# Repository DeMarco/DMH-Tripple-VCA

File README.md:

# DMH-Tripple-VCA
3x transistor based VCA on same panel

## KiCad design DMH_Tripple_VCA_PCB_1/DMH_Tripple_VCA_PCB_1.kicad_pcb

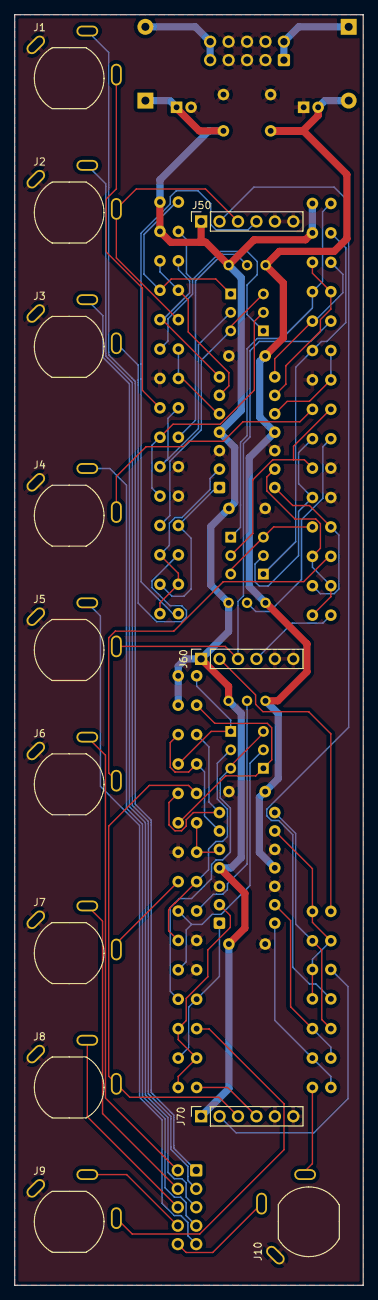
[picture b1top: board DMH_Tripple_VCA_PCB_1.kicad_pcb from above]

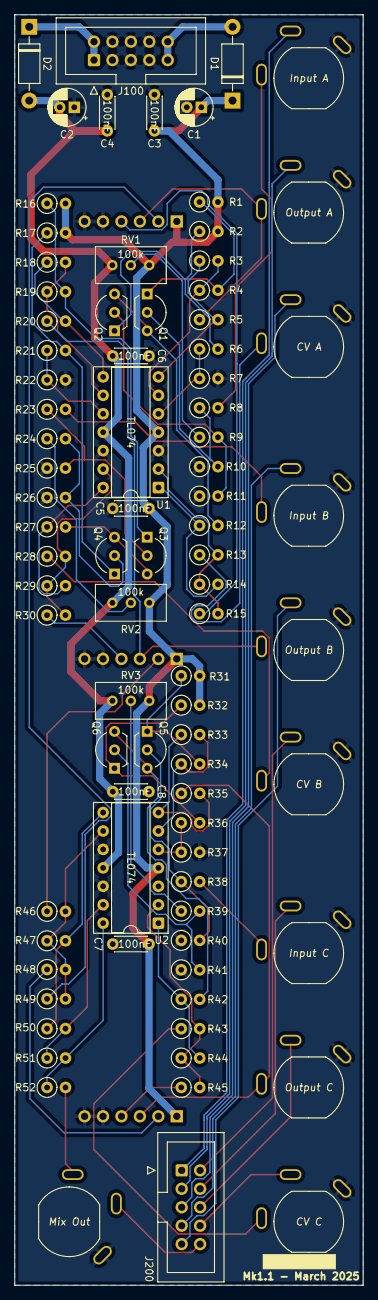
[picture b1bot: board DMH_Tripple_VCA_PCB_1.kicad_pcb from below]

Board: 2 copper layers, 48.0 x 175.0 mm, 88 parts (75 on the bottom side), 68 nets.

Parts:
C1, C2: 47uF; CP_Radial_D5.0mm_P2.00mm
C3, C4, C5, C6, C7, C8: 100nF; C_Disc_D4.3mm_W1.9mm_P5.00mm
D1: SB140+; D_DO-41_SOD81_P10.16mm_Horizontal
D2: SB140-; D_DO-41_SOD81_P10.16mm_Horizontal
J1, J2, J3, J4, J5, J6, J7, J8, J9, J10: TS_Jack_6.35mm_Sw; CUI_MJ-63052A
J50, J60, J70: Conn_01x06; PinSocket_1x06_P2.54mm_Vertical
J100: IDC_02x05; IDC-Header_2x05_P2.54mm_Vertical_Eurorack
J200: IDC_02x05; IDC-Header_2x05_P2.54mm_Vertical_BackBone
Q1, Q2, Q3, Q4, Q5, Q6: BC548; TO-92L_Inline_Wide
R1, R2, R16, R17, R31, R32: 20k; R_Axial_DIN0207_L6.3mm_D2.5mm_P2.54mm_Vertical
R3, R7, R8, R9, R13, R14, R15, R18, R22, R23, R24, R28, R29, R30, R33, R37, R38, R39, R43, R44, R45, R46, R47, R48, R49, R50, R51: 100k; R_Axial_DIN0207_L6.3mm_D2.5mm_P2.54mm_Vertical
R4, R6, R12, R19, R21, R27, R34, R36, R42: 10k; R_Axial_DIN0207_L6.3mm_D2.5mm_P2.54mm_Vertical
R5, R20, R35, R52: 1k; R_Axial_DIN0207_L6.3mm_D2.5mm_P2.54mm_Vertical
R10, R11, R25, R26, R40, R41: 100R; R_Axial_DIN0207_L6.3mm_D2.5mm_P2.54mm_Vertical
RV1, RV2, RV3: 100k; Potentiometer_Bourns_3296W_Vertical
U1, U2: TL074; DIP-14_W7.62mm_Socket

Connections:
+12V: C1.1, C3.1, C5.1, C7.1, D1.1 (K), J50.1, J60.1, J70.1, R1.2, R2.2, R16.2, R17.2, R31.2, R32.2, RV1.3, RV2.3, RV3.3, U1.4 (V+), U2.4 (V+)
-12V: C2.2, C4.2, C6.2, C8.2, D2.2 (A), RV1.1, RV2.1, RV3.1, U1.11 (V-), U2.11 (V-)
/Inputs and Outputs/CV A Jack: J3.T, R13.1
/Inputs and Outputs/CV B Jack: J6.T, R28.1
/Inputs and Outputs/CV C Jack: J9.T, R43.1
/Inputs and Outputs/Input A Jack: J1.T, R8.2
/Inputs and Outputs/Input B Jack: J4.T, R23.2
/Inputs and Outputs/Input C Jack: J7.T, R38.2
/Inputs and Outputs/Mix Out Jack: J10.T, R52.2
/Inputs and Outputs/Mute A Switch: J50.2, R49.1
/Inputs and Outputs/Mute B Switch: J60.2, R46.1
/Inputs and Outputs/Mute C Switch: J70.2, R48.1
/Inputs and Outputs/Offset A Pot: J50.4, R15.1
/Inputs and Outputs/Offset B Pot: J60.4, R30.1
/Inputs and Outputs/Offset C Pot: J70.4, R45.1
/Inputs and Outputs/Output A Jack: J2.T, J50.3, R5.1
/Inputs and Outputs/Output B Jack: J5.T, J60.3, R20.1
/Inputs and Outputs/Output C Jack: J8.T, J70.3, R35.1
GND: C1.2, C2.1, C3.2, C4.1, C5.2, C6.1, C7.2, C8.1, J1.S, J2.S, J3.S, J4.S, J5.S, J6.S, J7.S, J8.S, J9.S, J10.S, J50.5, J50.6, J60.5, J60.6, J70.5, J70.6, J100.2a, J100.2b, J100.3a, J100.3b, J100.4a, J100.4b, R7.2, R10.1, R11.1, R22.2, R25.1, R26.1, R37.2, R40.1, R41.1, U1.3 (+), U1.12 (+), U2.3 (+), U2.10 (+), U2.12 (+)
unnamed: D1.2 (A), J100.5a, J100.5b
unnamed: D2.1 (K), J100.1a, J100.1b
unnamed: J1.TN, J200.1
unnamed: J2.TN, J200.2
unnamed: J3.TN, J200.3
unnamed: J4.TN, J200.4
unnamed: J5.TN, J200.5
unnamed: J6.TN, J200.6
unnamed: J7.TN, J200.7
unnamed: J8.TN, J200.8
unnamed: J9.TN, J200.9
unnamed: J10.TN, J200.10
unnamed: Q1.2 (B), R8.1, R10.2
unnamed: Q1.1 (C), R1.1, R4.2
unnamed: Q1.3 (E), Q2.3 (E), R12.2
unnamed: Q2.2 (B), R9.2, R11.2
unnamed: Q2.1 (C), R2.1, R6.2
unnamed: Q3.2 (B), R23.1, R25.2
unnamed: Q3.1 (C), R16.1, R19.2
unnamed: Q3.3 (E), Q4.3 (E), R27.2
unnamed: Q4.2 (B), R24.2, R26.2
unnamed: Q4.1 (C), R17.1, R21.2
unnamed: Q5.2 (B), R38.1, R40.2
unnamed: Q5.1 (C), R31.1, R34.2
unnamed: Q5.3 (E), Q6.3 (E), R42.2
unnamed: Q6.2 (B), R39.2, R41.2
unnamed: Q6.1 (C), R32.1, R36.2
unnamed: R3.1, R5.2, U1.7
unnamed: R9.1, RV1.2
unnamed: R12.1, R14.2, U1.1
unnamed: R18.1, R20.2, U1.8
unnamed: R24.1, RV2.2
unnamed: R27.1, R29.2, U1.14
unnamed: R33.1, R35.2, U2.7
unnamed: R39.1, RV3.2
unnamed: R42.1, R44.2, U2.1
unnamed: R47.2, R50.1, U2.8
unnamed: R51.2, R52.1, U2.14
unnamed: R13.2, R14.1, R15.2, U1.2 (-)
unnamed: R6.1, R7.1, U1.5 (+)
unnamed: R3.2, R4.1, U1.6 (-)
unnamed: R21.1, R22.1, U1.10 (+)
unnamed: R18.2, R19.1, U1.9 (-)
unnamed: R28.2, R29.1, R30.2, U1.13 (-)
unnamed: R43.2, R44.1, R45.2, U2.2 (-)
unnamed: R36.1, R37.1, U2.5 (+)
unnamed: R33.2, R34.1, U2.6 (-)
unnamed: R46.2, R47.1, R48.2, R49.2, U2.9 (-)
unnamed: R50.2, R51.1, U2.13 (-)

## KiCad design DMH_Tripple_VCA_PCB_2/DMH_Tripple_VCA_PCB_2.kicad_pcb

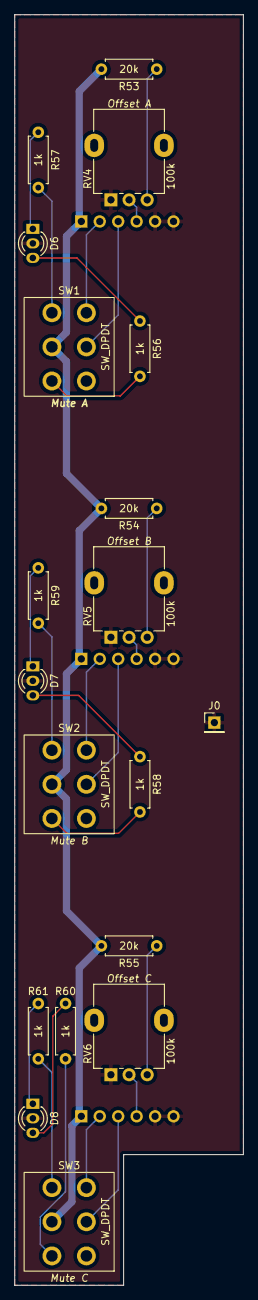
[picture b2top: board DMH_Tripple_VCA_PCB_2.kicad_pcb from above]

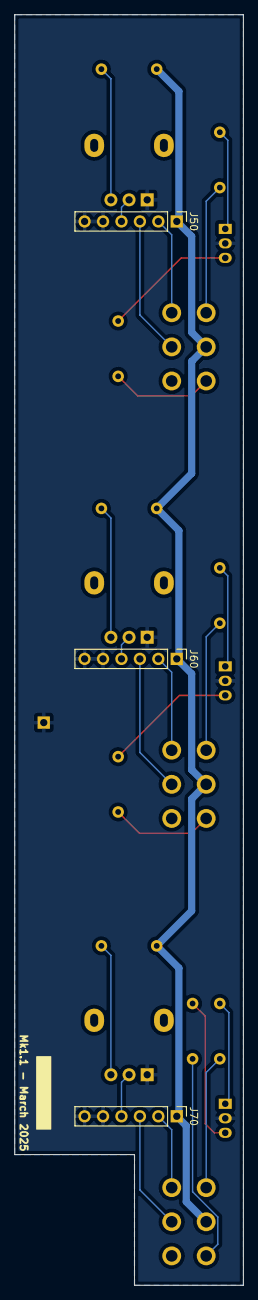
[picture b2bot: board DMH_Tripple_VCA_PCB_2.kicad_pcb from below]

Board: 2 copper layers, 31.5 x 175.0 mm, 22 parts (3 on the bottom side), 26 nets.

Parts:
D6, D7, D8: LED_Dual_AKA; LED_D3.0mm-2color
J0: Conn_01x01; PinHeader_1x01_P2.54mm_Vertical
J50, J60, J70: Conn_01x06; PinHeader_1x06_P2.54mm_Vertical
R53, R54, R55: 20k; R_Axial_DIN0207_L6.3mm_D2.5mm_P7.62mm_Horizontal
R56, R57, R58, R59, R60, R61: 1k; R_Axial_DIN0207_L6.3mm_D2.5mm_P7.62mm_Horizontal
RV4, RV5, RV6: 100k; Potentiometer_Alpha_RD901F-40-00D_Single_Vertical
SW1, SW2, SW3: SW_DPDT; Toggle_Switch_2_Poles_THT

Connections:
+12V: J50.1, J60.1, J70.1, R53.2, R54.2, R55.2, SW1.5 (B), SW2.5 (B), SW3.5 (B)
/Inputs and Outputs/Mute A Switch: J50.2, SW1.1 (A)
/Inputs and Outputs/Mute B Switch: J60.2, SW2.1 (A)
/Inputs and Outputs/Mute C Switch: J70.2, SW3.1 (A)
/Inputs and Outputs/Offset A Pot: J50.4, RV4.2
/Inputs and Outputs/Offset B Pot: J60.4, RV5.2
/Inputs and Outputs/Offset C Pot: J70.4, RV6.2
/Inputs and Outputs/Output A Jack: J50.3, SW1.2 (B)
/Inputs and Outputs/Output B Jack: J60.3, SW2.2 (B)
/Inputs and Outputs/Output C Jack: J70.3, SW3.2 (B)
GND: D6.2 (K), D7.2 (K), D8.2 (K), J0.1, J50.5, J50.6, J60.5, J60.6, J70.5, J70.6, RV4.1, RV5.1, RV6.1
unnamed: D6.1 (A1), R57.1
unnamed: D6.3 (A2), R56.1
unnamed: D7.1 (A1), R59.1
unnamed: D7.3 (A2), R58.1
unnamed: D8.1 (A1), R61.1
unnamed: D8.3 (A2), R60.1
unnamed: R53.1, RV4.3
unnamed: R54.1, RV5.3
unnamed: R55.1, RV6.3
unnamed: R56.2, SW1.6 (C)
unnamed: R57.2, SW1.4 (A)
unnamed: R58.2, SW2.6 (C)
unnamed: R59.2, SW2.4 (A)
unnamed: R60.2, SW3.6 (C)
unnamed: R61.2, SW3.4 (A)

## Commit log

2024-12-14 Created Panel project
2024-12-14 Added LED holes
2024-12-14 Created PCB projects
2024-12-14 Schematic in progress
2024-12-14 Finished Schematic
2024-12-14 PCB 1 component positioning ongoing
2024-12-14 Fixed LED position
2024-12-14 PCB 1 component positioning in progress
2024-12-15 PCB 1 Component placement done
2024-12-15 Adjusted OpAmp pinouts for placement
2024-12-15 Routing ongoing
2024-12-16 Started routing over with upright resistor fps
2024-12-27 sync libs
2024-12-27 Changed LEDs to bi-color
2025-02-21 Converted PCB 1 project to KiCad 9
2025-02-22 Routed PCB 1
2025-02-22 Corrected header locations and placed pcb2 comps
2025-02-22 Routed PCB 2
2025-02-23 Changed R14 R29 R44 to 100k
2025-03-16 Generated Gerbers
2025-03-17 Generated BoM
2025-04-19 Fixed mistakes in PCB 2
    - Inverted offset potentiometers pinout
    - LED resistors were too low, changed to 1k both colors
    - Regenerated PCB 2 gerbers accordingly
2025-04-19 Fixed another mistake
    U2C and U2D + and - inputs were inverted
